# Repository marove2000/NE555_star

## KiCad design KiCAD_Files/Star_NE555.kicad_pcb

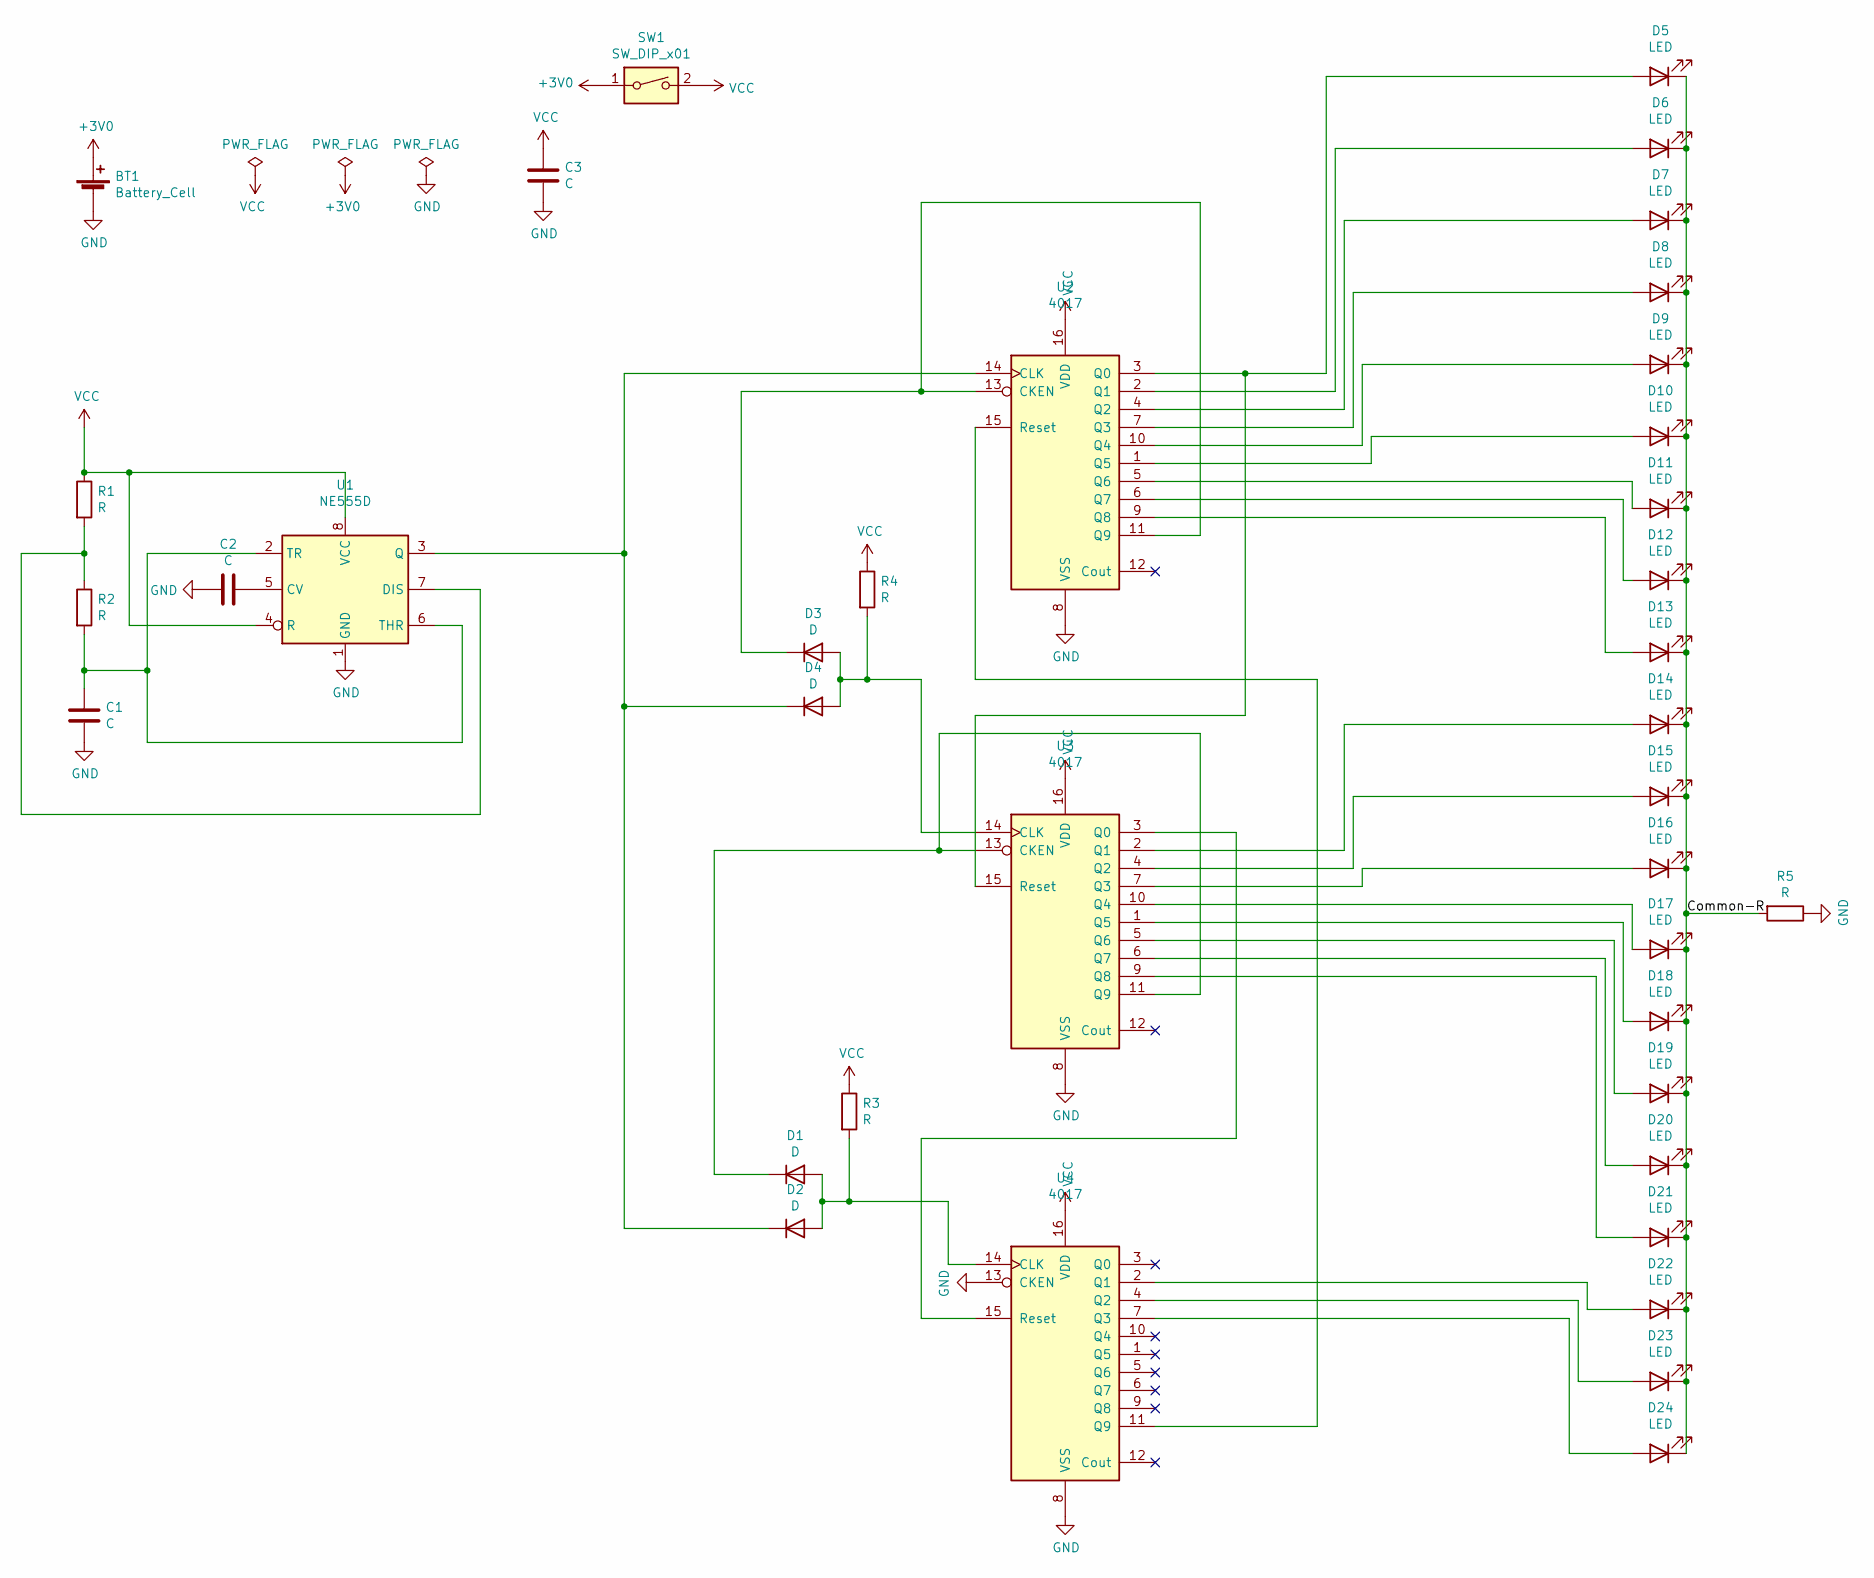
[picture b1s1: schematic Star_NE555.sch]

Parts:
BT1: Battery_Cell; BatteryHolder_Keystone_1060_1x2032
C1, C2, C3: C; C_0805_2012Metric_Pad1.18x1.45mm_HandSolder
D1, D2, D3, D4: D; D_0805_2012Metric_Pad1.15x1.40mm_HandSolder
D5, D6, D7, D8, D9, D10, D11, D12, D13, D14, D15, D16, D17, D18, D19, D20, D21, D22, D23, D24: LED; LED_0805_2012Metric_Pad1.15x1.40mm_HandSolder
R1, R2, R3, R4, R5: R; R_0805_2012Metric_Pad1.20x1.40mm_HandSolder
SW1: SW_DIP_x01; Push_Button
U1: NE555D; SOIC-8_3.9x4.9mm_P1.27mm
U2, U3, U4: 4017; SOP-16_4.4x10.4mm_P1.27mm

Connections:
+3V0: BT1.1 (+), SW1.1
/Common-R: D5.1 (K), D6.1 (K), D7.1 (K), D8.1 (K), D9.1 (K), D10.1 (K), D11.1 (K), D12.1 (K), D13.1 (K), D14.1 (K), D15.1 (K), D16.1 (K), D17.1 (K), D18.1 (K), D19.1 (K), D20.1 (K), D21.1 (K), D22.1 (K), D23.1 (K), D24.1 (K), R5.2
GND: BT1.2 (-), C1.2, C2.2, C3.2, R5.1, U1.1 (GND), U2.8 (VSS), U3.8 (VSS), U4.8 (VSS), U4.13 (CKEN)
unnamed: C1.1, R2.2, U1.2 (TR), U1.6 (THR)
unnamed: C2.1, U1.5 (CV)
unnamed: D1.1 (K), U3.11 (Q9), U3.13 (CKEN)
unnamed: D1.2 (A), D2.2 (A), R3.2, U4.14 (CLK)
unnamed: D2.1 (K), D4.1 (K), U1.3 (Q), U2.14 (CLK)
unnamed: D3.1 (K), U2.11 (Q9), U2.13 (CKEN)
unnamed: D3.2 (A), D4.2 (A), R4.2, U3.14 (CLK)
unnamed: D5.2 (A), U2.3 (Q0), U3.15 (Reset)
unnamed: D6.2 (A), U2.2 (Q1)
unnamed: D7.2 (A), U2.4 (Q2)
unnamed: D8.2 (A), U2.7 (Q3)
unnamed: D9.2 (A), U2.10 (Q4)
unnamed: D10.2 (A), U2.1 (Q5)
unnamed: D11.2 (A), U2.5 (Q6)
unnamed: D12.2 (A), U2.6 (Q7)
unnamed: D13.2 (A), U2.9 (Q8)
unnamed: D14.2 (A), U3.2 (Q1)
unnamed: D15.2 (A), U3.4 (Q2)
unnamed: D16.2 (A), U3.7 (Q3)
unnamed: D17.2 (A), U3.10 (Q4)
unnamed: D18.2 (A), U3.1 (Q5)
unnamed: D19.2 (A), U3.5 (Q6)
unnamed: D20.2 (A), U3.6 (Q7)
unnamed: D21.2 (A), U3.9 (Q8)
unnamed: D22.2 (A), U4.2 (Q1)
unnamed: D23.2 (A), U4.4 (Q2)
unnamed: D24.2 (A), U4.7 (Q3)
unnamed: R1.2, R2.1, U1.7 (DIS)
unnamed: U2.15 (Reset), U4.11 (Q9)
unnamed: U3.3 (Q0), U4.15 (Reset)
VCC: C3.1, R1.1, R3.1, R4.1, SW1.2, U1.4 (R), U1.8 (VCC), U2.16 (VDD), U3.16 (VDD), U4.16 (VDD)

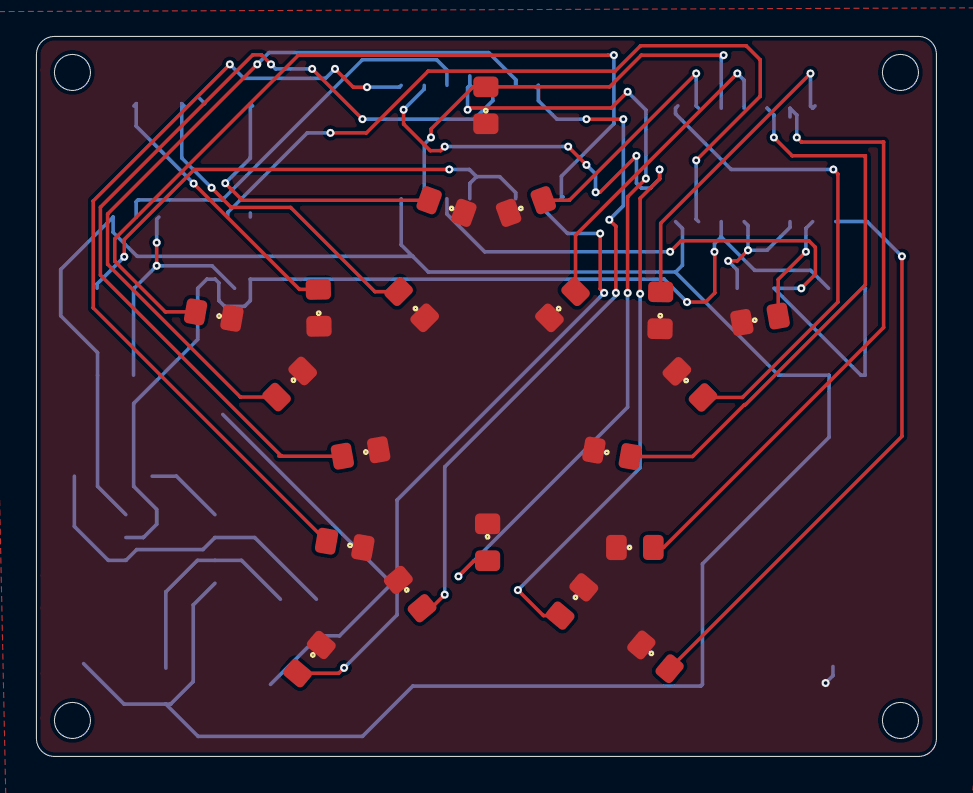
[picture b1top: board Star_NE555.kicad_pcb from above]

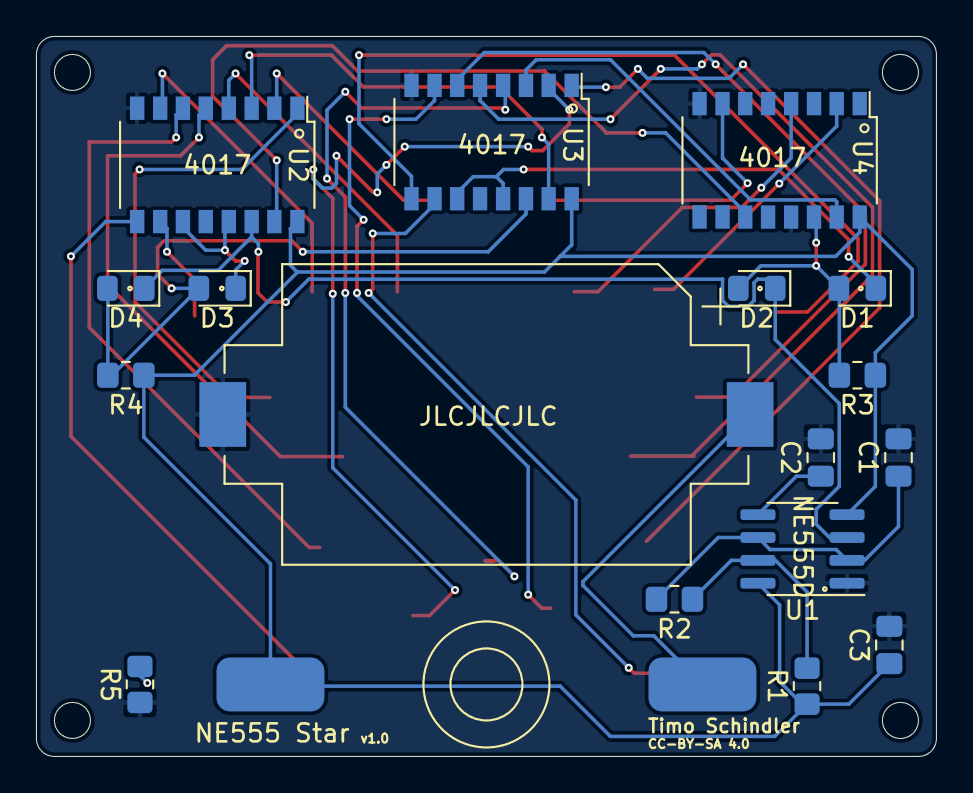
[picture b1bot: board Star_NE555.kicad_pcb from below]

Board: 2 copper layers, 50.0 x 40.0 mm, 40 parts (18 on the bottom side), 34 nets.

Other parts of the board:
Ref**: Val**; star_small
Ref**#2: Val**; star

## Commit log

2021-01-23 inital commit

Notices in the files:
KiCAD_Files/Star_NE555.kicad_pcb:
CC-BY-SA 4.0
